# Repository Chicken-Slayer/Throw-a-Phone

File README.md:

# Throw-a-Phone
Have you ever forgotten your phone at home, and just kept your SIM card along? Me too!
This device aims to solve this common problem faced by us in our daily lives.

In all seriousness, this is a device for people who need absolutely no distractions, or simply a cheap device that can be bought to simply make phone calls without any drama.

## How it works:
Inside the case, there is an ESP32 C3 SUPERMINI, which is compact and affordable - perfect for this use case. Basically, the device uses a 12 key matrix as input, which can be used to enter phone numbers and answer/end calls. The calls are handled using a SIM800L GSM module connected to an external antenna. Due to the hardware used, it can only support 2G networks, which are outdated and may not be available everywhere. 

## PCB:
Here's the Schematic and the PCB:

## Enclosure:
The components are placed within a 3D printed enclosure. The PCB is held in place with round inserts set in place in both the PCB and the Enclosure. 

It has two separate pieces: 
- The top cover, featuring space for the keys, power switch, screen, and audio I/O
- The base, which has obtrusions designed to hold the PCB in place, as well as clearance for an external antenna and charging port.

The two pieces are secured using hot glue.

## Firmware:
The device is coded in C, and makes/receives phone calls by communicating with the GSM module through the UART interface. A key matrix is used to input the numbers and Adafruit libraries are used to control the OLED Display. Different states of the phone have been defined, in which different output is displayed on the OLED.

## Features:
- Making and receiving phone calls

## Replication Guide:
This project is quite easy to replicate hardware-wise, but the software part comes out to be more complicated.
1. Start off by wiring the charging board output to the rocker switch, and then the switch to the ESP32 and the GSM module. The GSM module cannot run on 3.3V supplied by ESP32, so it needs to be powered directly by the battery.
2. Solder the buttons and the OLED display on to the PCB, making sure that the diodes are in the right direction (COL2ROW).
3. Solder the ESP32 module to the PCB and connect the RX, TX and GPIO0 pins to the corresponding ones on the GSM modules.
4. Wire the speaker and the microphone directly to the GSM module and connect the PCB antenna (comes bundled with GSM module).
5. Connect the battery to the charging board power input. Make sure to check polarity.
6. Load up the firmware on to the ESP32 board, making sure to check the pin definitions in the code.
7. Secure the components in place, holding the PCB using the round insertions in the case, and hot gluing remaining components in their respective places. On the top part of the case, space has been given for inserting the microphone, speaker, and rocker switch. There are holes on the bottom part of the case to route the PCB antenna outside and connect the charging module to a USB cable. 

## BOM:
| Product Name                         | Product Link                                                                                    | Unit Price | Amount | Total  | Remarks                        |
|--------------------------------------|-------------------------------------------------------------------------------------------------|------------|--------|--------|--------------------------------|
| PCB                                  | https://jlcpcb.com/                                                                             | $2.00      | 1      | $11.47 |                                |
| SIM800L GPRS GSM Module              | https://roboticsdna.in/product/sim800l-module/                                                  | $3.10      | 1      | $4.04  | Delivery costs and taxes apply |
| 3.7V 1500 mAh LiPo Battery           | https://robu.in/product/1500mah-pcm-protected-micro-li-po-battery                               | $2.96      | 1      | $2.96  |                                |
| Tactile Push Button Switch           | https://robu.in/product/6x6x5-tactile-push-button-switch                                        | $0.014     | 12     | $0.28  | Only in packs of 10            |
| Microphone                           | https://robu.in/product/microphone-97mm-pack-of-3                                               | $0.20      | 1      | $0.58  | Only in packs of 3             |
| TP4056 Li-ion battery charging board | https://robu.in/product/tp4056-1a-lipo-battery-charging-board-micro-usb-with-current-protection | $0.12      | 1      | $0.12  |                                |
| 28mm Trumpet Speaker                 | https://robu.in/product/0-5w-8ohm-trumpet-speaker-diameter-28mm                                 | $0.30      | 1      | $0.30  |                                |
| SPST Rocker Switch                   | https://robu.in/product/spst-rocker-switch-pack-of-3                                            | $0.15      | 1      | $0.15  |                                |
| ESP32-C3 SUPERMINI                   | https://robu.in/product/esp32-c3-development-board-with-soldering                               | $2.59      | 1      | $2.59  |                                |
| 0.91 inch I2C OLED Display           | https://roboticsdna.in/product/0-91-inch-iic-4-pin-oled-display-module-ssd1306-white/           | $1.66      | 1      | $2.60  | Delivery costs and taxes apply |
| M2x10mm CSK Countersunk Philips head bolt| https://robu.in/product/easymech-ss-304-csk-countersunk-philips-head-m2-x-10-mm-bolt-25-pcs/| $1.48      | 4      | $1.48  | Only in packs of 25            |
|                                      |                                                                                                 |            | TOTAL  | $25.09 |                                |
## Zine:

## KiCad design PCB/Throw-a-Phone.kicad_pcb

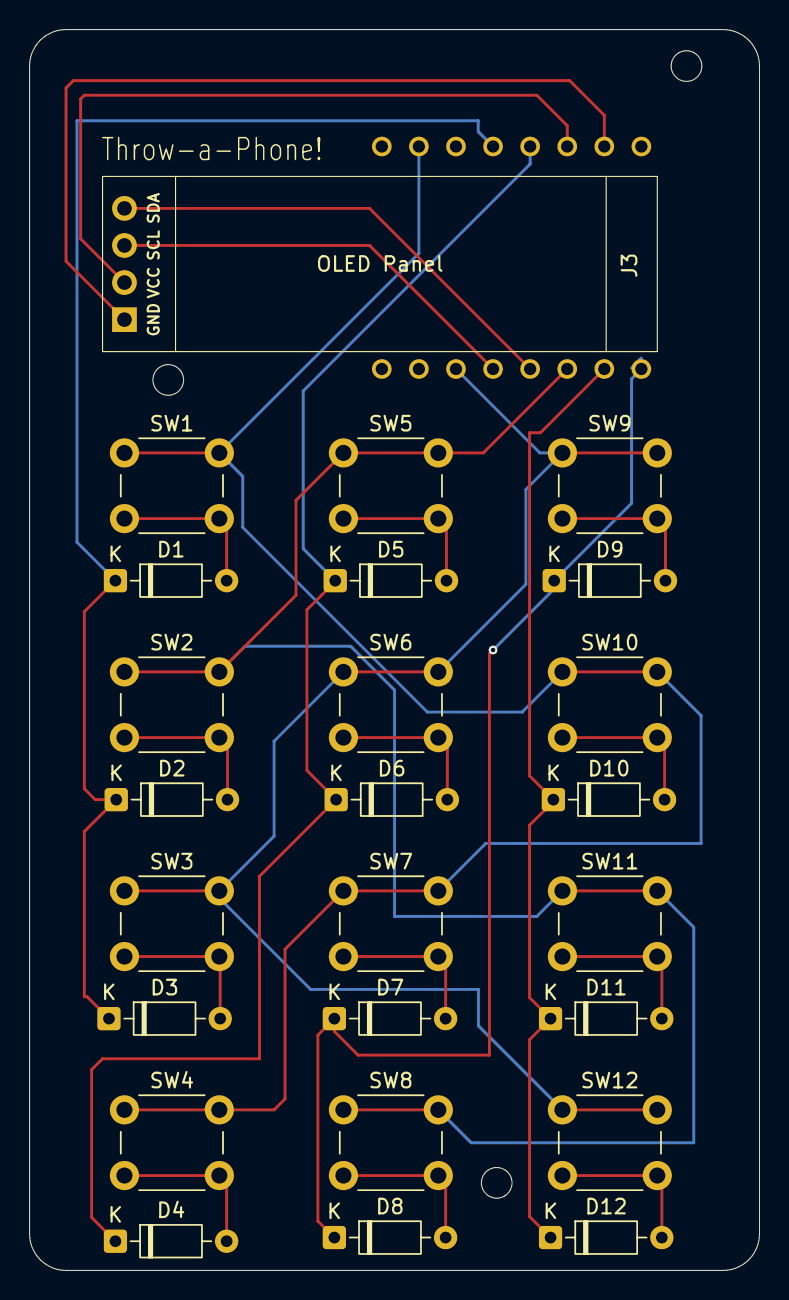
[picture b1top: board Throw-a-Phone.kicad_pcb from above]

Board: 2 copper layers, 50.0 x 85.0 mm, 26 parts (1 on the bottom side), 23 nets.

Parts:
D1, D2, D3, D4, D5, D6, D7, D8, D9, D10, D11, D12: 1N4148; D_DO-35_SOD27_P7.62mm_Horizontal
J3: Conn_01x04_Pin; SSD1306-0.91-OLED-4pin-128x32
SW1, SW2, SW3, SW4, SW5, SW6, SW7, SW8, SW9, SW10, SW11, SW12: SW_Push; SW_PUSH_6mm_H5mm
U1: ESP32-C3_SUPERMINI_TH; MODULE_ESP32-C3_SUPERMINI_TH

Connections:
+3V3: J3.2, U1.3.3 (3V3)
COL0: SW1.1, SW4.1, SW7.1, SW10.1, U1.1 (GPIO1)
COL1: SW2.1, SW5.1, SW8.1, SW11.1, U1.7 (GPIO7)
COL2: SW3.1, SW6.1, SW9.1, SW12.1, U1.10 (GPIO10)
GND: J3.1, U1.G (GND)
unnamed: D1.2 (A), SW1.2
unnamed: D2.2 (A), SW2.2
unnamed: D3.2 (A), SW3.2
unnamed: D4.2 (A), SW4.2
unnamed: D5.2 (A), SW5.2
unnamed: D6.2 (A), SW6.2
unnamed: D7.2 (A), SW7.2
unnamed: D8.2 (A), SW8.2
unnamed: D9.2 (A), SW9.2
unnamed: D10.2 (A), SW10.2
unnamed: D11.2 (A), SW11.2
unnamed: D12.2 (A), SW12.2
OLED_SCL: J3.3, U1.9 (GPIO9)
OLED_SDA: J3.4, U1.8 (GPIO8)
ROW0: D1.1 (K), D2.1 (K), D3.1 (K), U1.3 (GPIO3)
ROW1: D4.1 (K), D5.1 (K), D6.1 (K), U1.4 (GPIO4)
ROW2: D7.1 (K), D8.1 (K), D9.1 (K), U1.5 (GPIO5)
ROW3: D10.1 (K), D11.1 (K), D12.1 (K), U1.6 (GPIO6)

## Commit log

2026-03-29 Designed Schematic
2026-04-04 Made PCB, fixed design
2026-04-19 Made enclosure, edited PCB
2026-04-21 Updated readme, added images. Fixed PCB edge cuts
2026-04-21 Updated Firmware
2026-04-26 Typing functionality
2026-04-26 Add key control
2026-04-26 Add comments
2026-04-26 Added zine page, removed old. Added 3D model.
2026-04-27 Update PCB, readme. Create gerbers
2026-04-27 Update BOM
2026-04-27 Fix quantities in BOM
2026-04-27 Update BOM, changed directory
2026-04-27 Fix BOM final
2026-04-27 Update zine image
2026-04-27 Add replication guide
2026-05-04 Add Zine pdf
2026-05-06 Update firmware
2026-05-07 Add GSM module communication
2026-05-10 Fix directory nesting
2026-05-22 Update README, change zine
2026-05-22 Add CAD design for production
2026-05-22 Remove history dir
